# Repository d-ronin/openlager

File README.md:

STM32F4 based logging dongle for **HIGH RATE** logging

This project is inspired by [OpenLog](https://github.com/sparkfun/OpenLog).

*Why do something new?*  To attain higher rates!  The **openlager** hardware can accept data at high rates using slave SPI or fast async serial.  It uses a 4-wide SDIO interface to the card to support higher peak logging rates.  And the reasonable amount of memory buffer on the STM32F411 lets us ride out times when the SD card is busy erasing or doing other housekeeping without losing data.

The **openlager** hardware design and firmware are produced by the [dRonin](http://dronin.org) project, which produces high-quality flight controller software for drone racing and autonomous flight.  To log everything that's happening in a lossless fashion, high rate logs are required.  But we anticipate it being useful for a wide variety of applications.

# Licenses

The **openlager** hardware in `hardware/` is licensed under a Creative Commons Attribution 4.0 International License (CC BY 4.0), as contained in `hardware/LICENSE.txt`

The **openlager** firmware (and bootloader) in `src/`, `loader/`, and `shared/` is licensed under a simplified BSD license as found in `src/LICENSE.txt`

The openlager **logo** may only be used with permission from the dRonin project.

The **fatfs** library in `libs/fatfs` is licensed under the one-clause BSD license as found in the source files in that directory.

The **STM32F4xx_StdPeriph_Driver** library in `libs/STM32F4xx_StdPeriph_Driver` is largely licensed under a restrictive license that limits its usage to ST family processors.  To use this software on non-ST parts, the dependency on this library code must be removed.  Portions of this code (the `core_cm*` include headers) are licensed under a permissive 3 clause BSD license from ARM, as noted in the individual files.

The **mmcreg.h** file from FreeBSD in `libs/inc` is licensed under a simplified BSD license.

The **jsmn** library in `libs` is licensed under the MIT license.

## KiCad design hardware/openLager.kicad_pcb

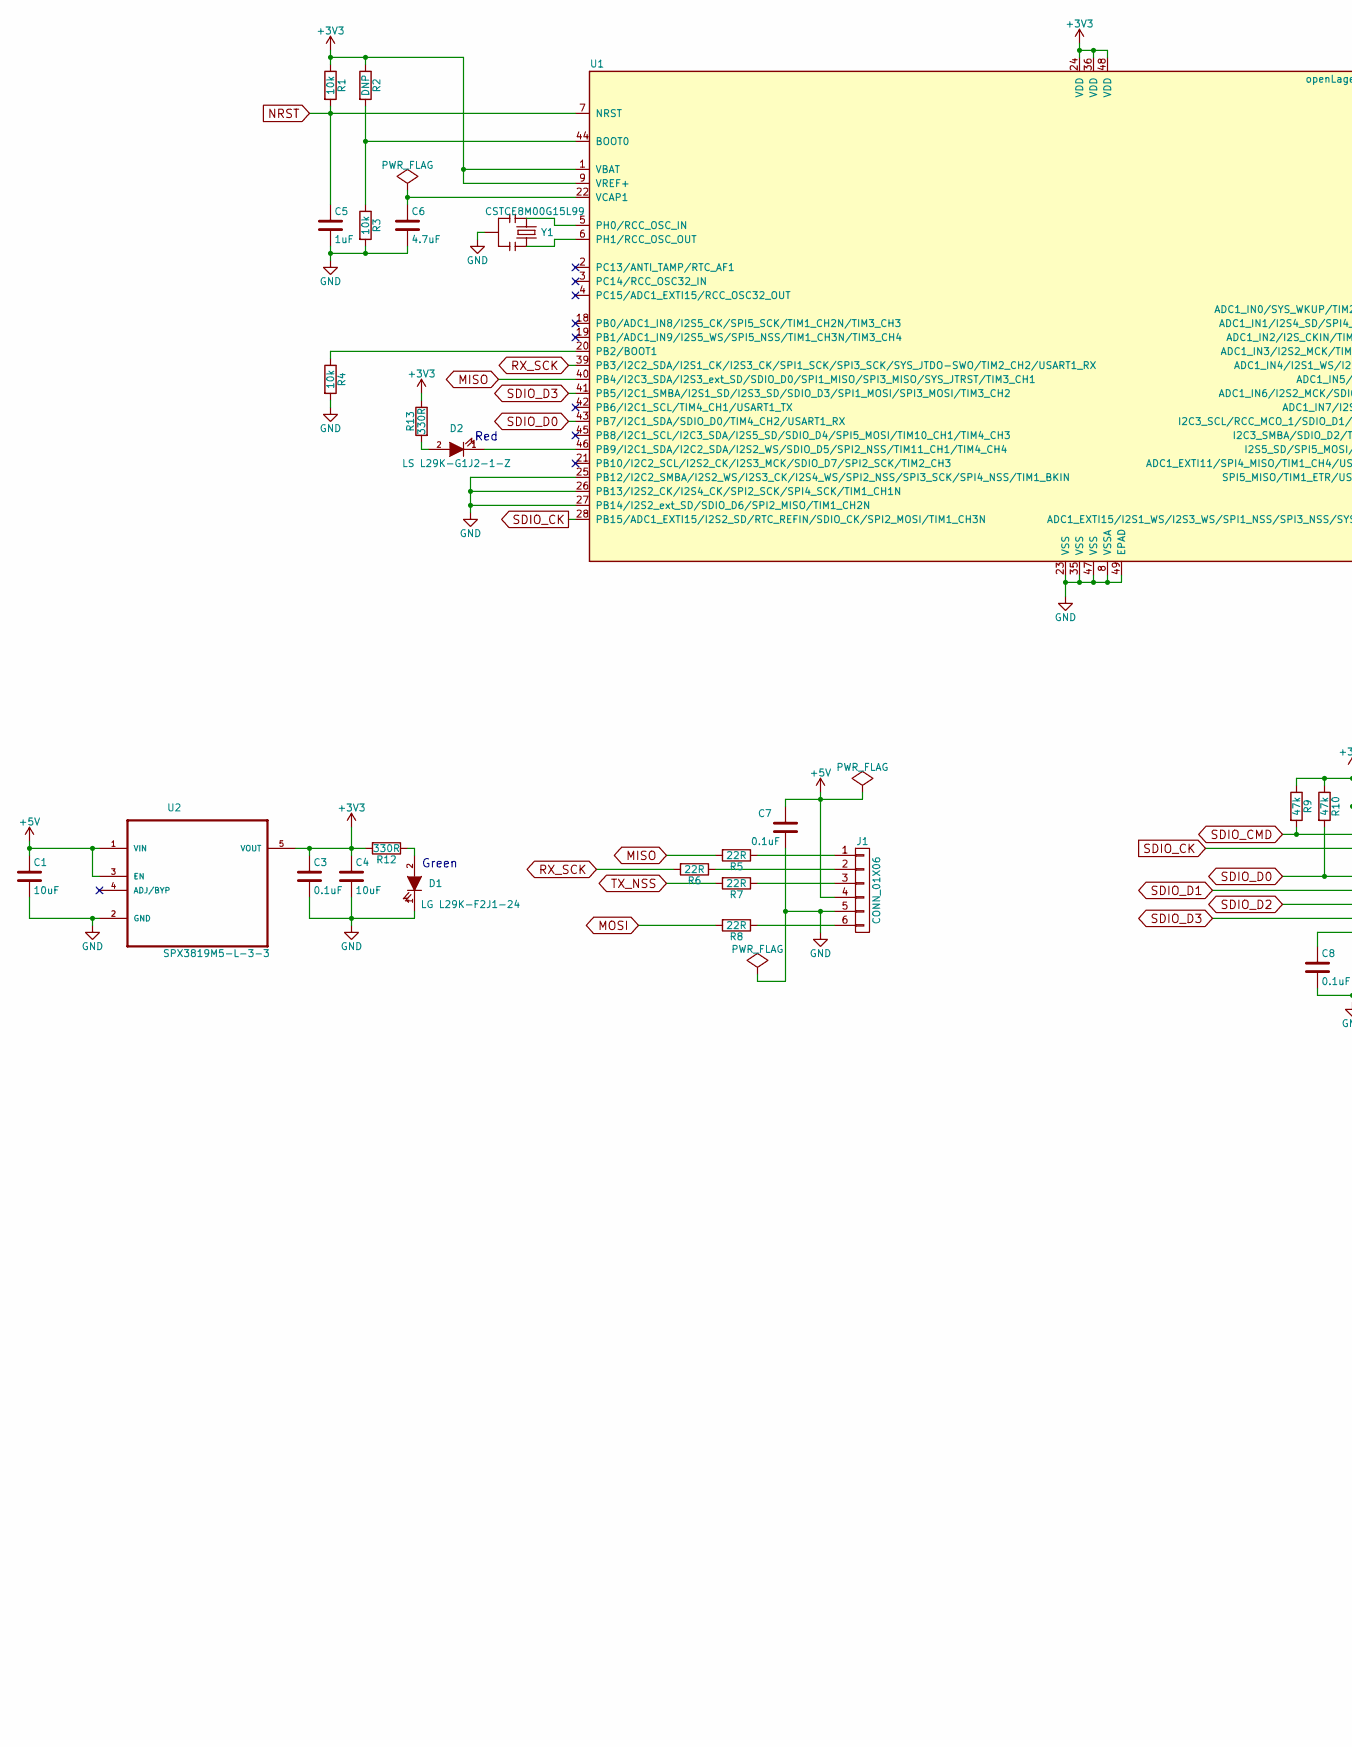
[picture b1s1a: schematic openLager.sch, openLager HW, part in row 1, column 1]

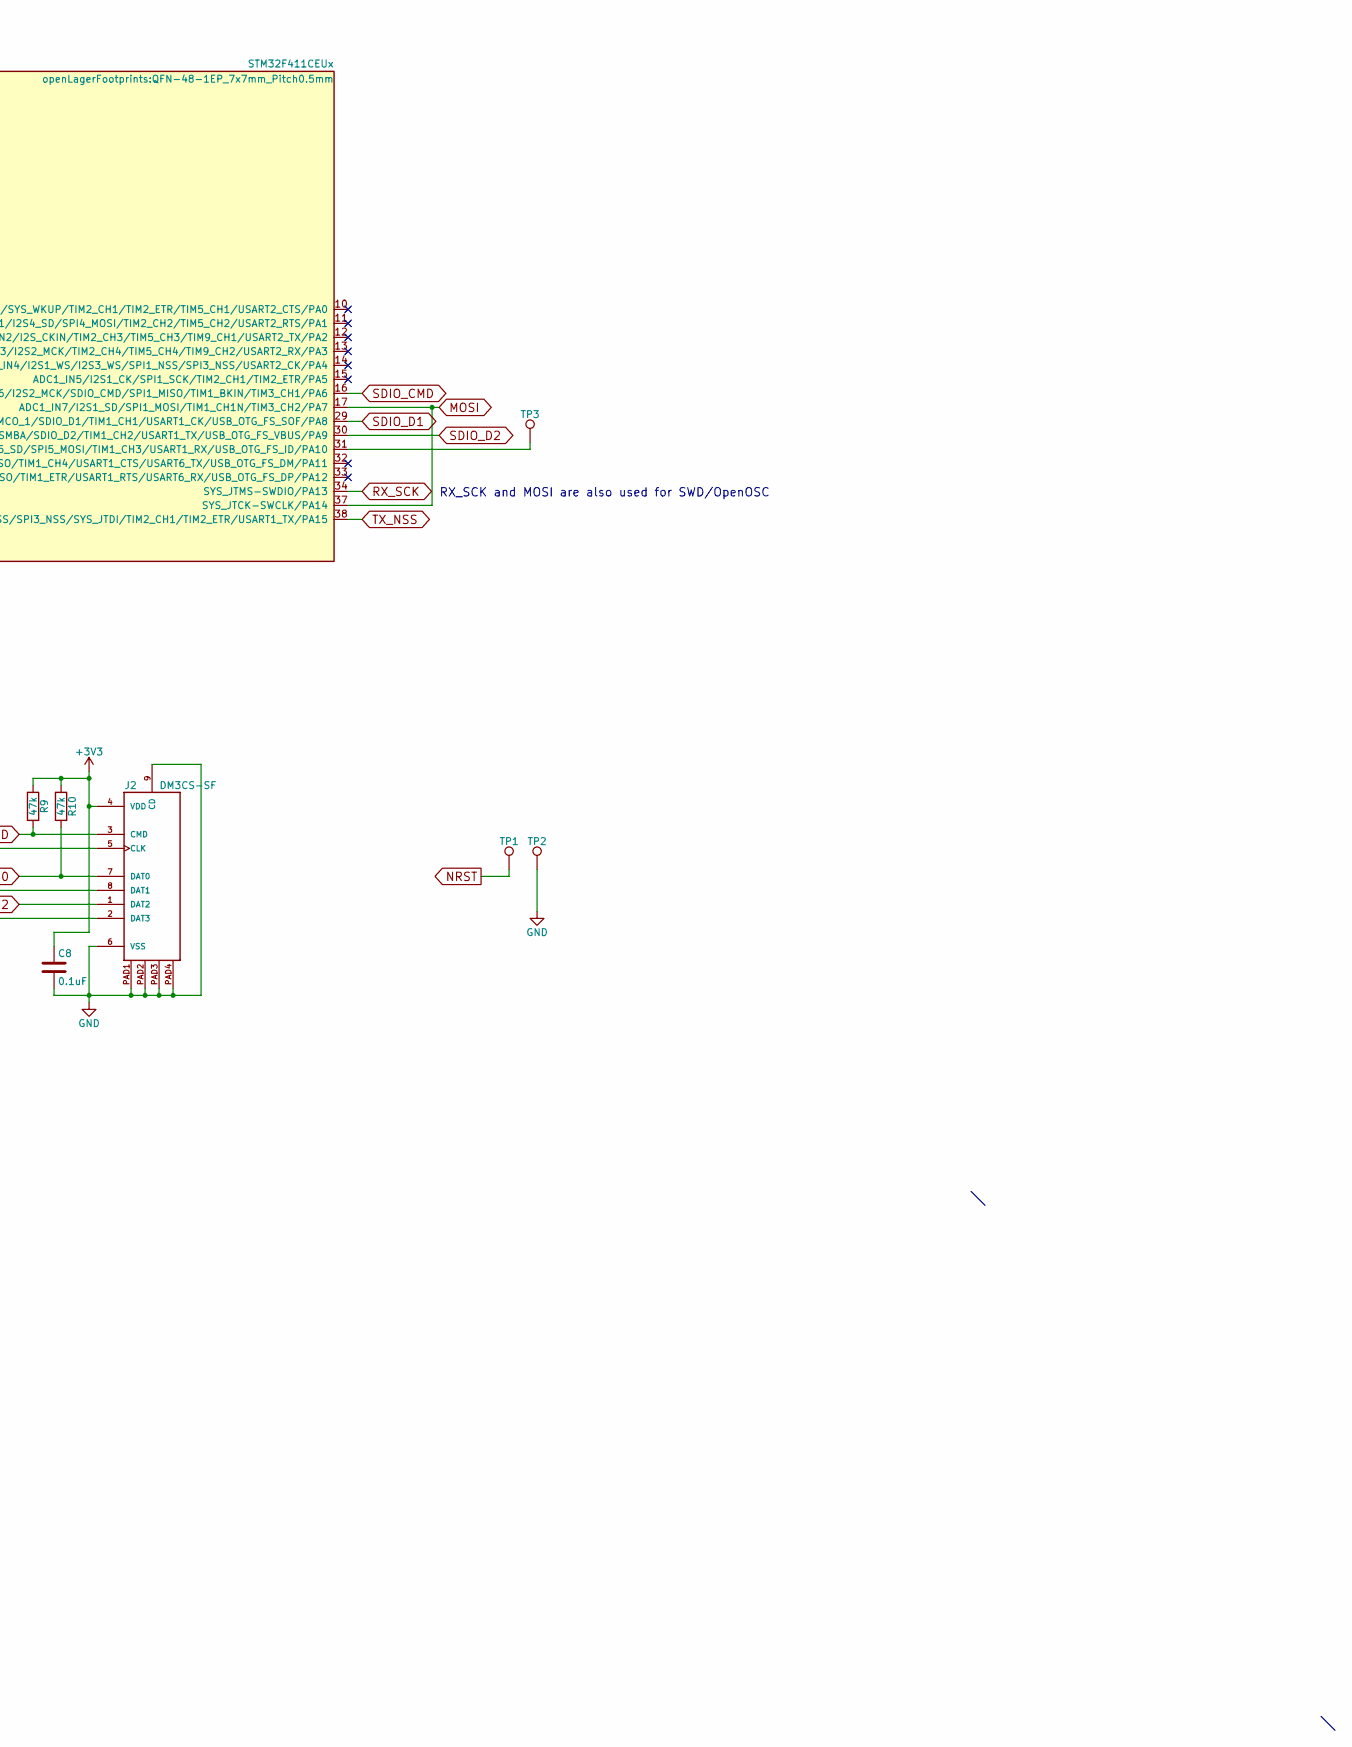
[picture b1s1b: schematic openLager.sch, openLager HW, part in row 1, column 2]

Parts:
C1, C4: 10uF; C_0402; Mfg PN CL05A106MP5NUNC
C3, C7, C8: 0.1uF; C_0402; Mfg PN GRM155R70J104KA01D
C5: 1uF; C_0402; Mfg PN GRM155R70J105MA12D
C6: 4.7uF; C_0402; Mfg PN CL05A475MQ5NQNC
D1: LG L29K-F2J1-24; LED_0603; Mfg PN LG L29K-F2J1-24
D2: LS L29K-G1J2-1-Z; LED_0603; Mfg PN LS L29K-G1J2-1-Z
J1: CONN_01X06; Socket_Strip_Straight_1x06; Mfg PN DNP
J2: DM3CS-SF; HRS_DM3CS-SF; Mfg PN DM3CS-SF
R1, R3, R4: 10k; R_0402; Mfg PN RC0402JR-0710KL
R2: DNP; R_0402; Mfg PN DNP
R5, R6, R7, R8: 22R; R_0402; Mfg PN RC0402JR-0722RL
R9, R10: 47k; R_0402; Mfg PN RC0402JR-0747KL
R12, R13: 330R; R_0402; Mfg PN RC0402JR-07330RL
TP1, TP2, TP3: TEST_1P; TP; Mfg PN DNP
U1: STM32F411CEUx; QFN-48-1EP_7x7mm_Pitch0.5mm; Mfg PN STM32F411CEU6
U2: SPX3819M5-L-3-3; SOT95P280X145-5N; Mfg PN SPX3819M5-L-3-3/TR
Y1: CSTCE8M00G15L99; X3-SMD-3.6X1.3X0.8MM; Mfg PN CSTCE8M00G15L99-R0

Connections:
+3V3: C3.1, C4.1, C8.1, J2.4 (VDD), R1.1, R2.1, R9.1, R10.1, R12.2, R13.1, U1.1 (VBAT), U1.9 (VREF+), U1.24 (VDD), U1.36 (VDD), U1.48 (VDD), U2.5 (VOUT)
+5V: C1.1, C7.1, J1.4, U2.1 (VIN), U2.3 (EN)
GND: C1.2, C3.2, C4.2, C5.2, C6.2, C7.2, C8.2, D1.1 (K), J1.5, J2.6 (VSS), J2.9 (CD), J2.PAD1, J2.PAD2, J2.PAD3, J2.PAD4, R3.2, R4.2, TP2.1, U1.8 (VSSA), U1.23 (VSS), U1.25 (PB12/I2C2_SMBA/I2S2_WS/I2S3_CK/I2S4_WS/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), U1.26 (PB13/I2S2_CK/I2S4_CK/SPI2_SCK/SPI4_SCK/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), U1.27 (PB14/I2S2_ext_SD/SDIO_D6/SPI2_MISO/TIM1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), U1.35 (VSS), U1.47 (VSS), U1.49 (EPAD), U2.2 (GND), Y1.2
MISO: R5.2, U1.40 (PB4/I2C3_SDA/I2S3_ext_SD/SDIO_D0/SPI1_M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)
MOSI: R8.2, U1.17 (ADC1_IN7/I2S1_SD/SPI1_MOSI/TIM1_CH1N/TI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), U1.37 (SYS_JTCK-SWCLK/PA14)
NRST: C5.1, R1.2, TP1.1, U1.7 (NRST)
unnamed: C6.1, U1.22 (VCAP1)
unnamed: D1.2 (A), R12.1
unnamed: D2.1 (K), U1.46 (PB9/I2C1_SDA/I2C2_SDA/I2S2_WS/SDIO_D5/S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)
unnamed: D2.2 (A), R13.2
unnamed: J1.1, R5.1
unnamed: J1.2, R6.1
unnamed: J1.3, R7.1
unnamed: J1.6, R8.1
unnamed: R2.2, R3.1, U1.44 (BOOT0)
unnamed: R4.1, U1.20 (PB2/BOOT1)
unnamed: TP3.1, U1.31 (I2S5_SD/SPI5_MOSI/TIM1_CH3/USART1_RX/US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)
unnamed: U1.5 (PH0/RCC_OSC_IN), Y1.1
unnamed: U1.6 (PH1/RCC_OSC_OUT), Y1.3
RX_SCK: R6.2, U1.34 (SYS_JTMS-SWDIO/PA13), U1.39 (PB3/I2C2_SDA/I2S1_CK/I2S3_CK/SPI1_SCK/S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)
SDIO_CK: J2.5 (CLK), U1.28 (PB15/ADC1_EXTI15/I2S2_SD/RTC_REFIN/SDIO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)
SDIO_CMD: J2.3 (CMD), R9.2, U1.16 (ADC1_IN6/I2S2_MCK/SDIO_CMD/SPI1_MISO/TI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)
SDIO_D0: J2.7 (DAT0), R10.2, U1.43 (PB7/I2C1_SDA/SDIO_D0/TIM4_CH2/USART1_RX)
SDIO_D1: J2.8 (DAT1), U1.29 (I2C3_SCL/RCC_MCO_1/SDIO_D1/TIM1_CH1/USA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)
SDIO_D2: J2.1 (DAT2), U1.30 (I2C3_SMBA/SDIO_D2/TIM1_CH2/USART1_TX/US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)
SDIO_D3: J2.2 (DAT3), U1.41 (PB5/I2C1_SMBA/I2S1_SD/I2S3_SD/SDIO_D3/S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)
TX_NSS: R7.2, U1.38 (ADC1_EXTI15/I2S1_WS/I2S3_WS/SPI1_NSS/SP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)

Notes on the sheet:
Green
Red
RX_SCK and MOSI are also used for SWD/OpenOSC

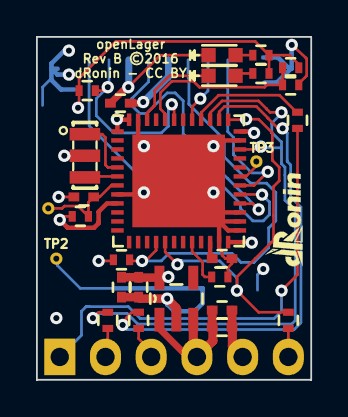
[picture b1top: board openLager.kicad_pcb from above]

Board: 4 copper layers, 15.2 x 19.0 mm, 29 parts (1 on the bottom side), 27 nets.

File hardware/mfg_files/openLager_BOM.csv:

Reference, Quantity, Value, Footprint, Datasheet, Mfg Name, Mfg PN, Link
C1 C4 ,2,10uF,openLagerFootprints:C_0402,http://datasheet.octopart.com/CL05A106MP5NUNC-Samsung-datash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,Samsung,CL05A106MP5NUNC,https://octopart.com/cl05a106mp5nunc-samsung-22457395
C5 ,1,1uF,openLagerFootprints:C_0402,http://datasheet.octopart.com/GRM-Series-Murata-datasheet-fa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,Murata,GRM155R70J105MA12D,https://octopart.com/grm155r70j105ma12d-murata-23261089
C6 ,1,4.7uF,openLagerFootprints:C_0402,http://www.samsungsem.com/kr/support/product-search/mlcc/__i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,Samsung,CL05A475MQ5NQNC,https://octopart.com/cl05a475mq5nqnc-samsung-24957780
C3 C7 C8 ,3,0.1uF,openLagerFootprints:C_0402,http://datasheet.octopart.com/GRM155R70J104KA01D-Murata-data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,Murata,GRM155R70J104KA01D,https://octopart.com/grm155r70j104ka01d-murata-17930200
D1 ,1,LG L29K-F2J1-24,openLagerFootprints:LED_0603,http://datasheet.octopart.com/LG-L29K-F2J1-24-Osram-datashee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,Osram Opto,LG L29K-F2J1-24,https://octopart.com/lg+l29k-f2j1-24-osram+opto-31119809
D2 ,1,LS L29K-G1J2-1-Z,openLagerFootprints:LED_0603,http://datasheet.octopart.com/Q65110A1757-Osram-Opto-datashe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,Osram Opto,LS L29K-G1J2-1-Z,https://octopart.com/ls+l29k-g1j2-1-z-osram+opto-31093939
J1 ,1,CONN_01X06,openLagerFootprints:Socket_Strip_Straight_1x06,DNP,DNP,DNP,DNP
J2 ,1,DM3CS-SF,openLagerFootprints:HRS_DM3CS-SF,http://datasheet.octopart.com/DM3CS-SF-Hirose-datasheet-6229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,Hirose,DM3CS-SF,https://octopart.com/dm3cs-sf-hirose-44525751
R1 R3 R4 ,3,10k,openLagerFootprints:R_0402,http://datasheet.octopart.com/RC0402JR-0710KL-Yageo-datashee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,Yageo,RC0402JR-0710KL,https://octopart.com/rc0402jr-0710kl-yageo-55458470
R12 R13 ,2,330R,openLagerFootprints:R_0402,http://datasheet.octopart.com/RC0402JR-07330RL-Yageo-datashe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,Yageo,RC0402JR-07330RL,https://octopart.com/rc0402jr-07330rl-yageo-40021082
R2 ,1,DNP,openLagerFootprints:R_0402,DNP,DNP,DNP,DNP
R5 R6 R7 R8 ,4,22R,openLagerFootprints:R_0402,http://datasheet.octopart.com/RC0402JR-0722RL-Yageo-datashee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,Yageo,RC0402JR-0722RL,https://octopart.com/rc0402jr-0722rl-yageo-1173206
R10 R9 ,2,47k,openLagerFootprints:R_0402,http://datasheet.octopart.com/RC0402JR-0747KL-Yageo-datashee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,Yageo,RC0402JR-0747KL,https://octopart.com/rc0402jr-0747kl-yageo-39834460
TP1 ,1,TEST_1P,openLagerFootprints:Socket_Strip_Straight_1x01,DNP,DNP,DNP,DNP
TP2 TP3 ,2,TEST_1P,openLagerFootprints:TP,DNP,DNP,DNP,DNP
U1 ,1,STM32F411CEUx,openLagerFootprints:QFN-48-1EP_7x7mm_Pitch0.5mm,http://datasheet.octopart.com/STM32F411CEU6-STMicroelectroni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,ST Microelectronics,STM32F411CEU6,https://octopart.com/stm32f411ceu6-stmicroelectronics-47202664
U2 ,1,SPX3819M5-L-3-3,openLagerFootprints:SOT95P280X145-5N,http://datasheet.octopart.com/SPX3819M5-L-3-3-TR-Exar-datash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,Exar,SPX3819M5-L-3-3/TR,https://octopart.com/spx3819m5-l-3-3%2Ftr-exar-9290124
Y1 ,1,CSTCE8M00G15L99,openLagerFootprints:X3-SMD-3.6X1.3X0.8MM,http://datasheet.octopart.com/CSTCE8M00G15L99-R0-Murata-data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,Murata,CSTCE8M00G15L99-R0,https://octopart.com/cstce8m00g15l99-r0-murata-17751576

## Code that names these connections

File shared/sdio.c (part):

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	// Clocks programmed elsewhere and peripheral/GPIO clock enabled already

	// program GPIO / PinAF
	// SDIO_CK=PB15            SDIO_CMD=PA6
	// SDIO_D0=PB7 SDIO_D1=PA8 SDIO_D2=PA9 SDIO_D3=PB5

	sd_initpin(GPIOA, 6);
	sd_initpin(GPIOA, 8);
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
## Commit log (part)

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2016-04-17 readme: enhance, add logo artwork
2016-04-17 readme: enhance, add logo artwork (#1)
2016-04-17 argh, touch up a dumb typo.
2016-04-17 argh, touch up a dumb typo. (#2)
2016-04-17 introduce fatfs library from upstream R0.12 (#3)
    retrieved from http://elm-chan.org/fsw/ff/00index_e.html
    http://elm-chan.org/fsw/ff/ff12.zip
2016-04-17 Import STM32F4xx_StdPeriph_Driver.
    License was saved from
    http://www.st.com/software_license_agreement_liberty_v2
2016-04-17 Import STM32F4xx_StdPeriph_Driver. (#4)
    License was saved from
    http://www.st.com/software_license_agreement_liberty_v2
2016-04-17 Add license file and license info, reorg tree (#5)
2016-04-18 manually bring in other parts of ST libs
    This stuff was in cmsis_system.
2016-04-18 readme: improve license description
2016-04-18 Add a minimal makefile to compile stuff.
    Does not properly link, linker script, do startup code, etc.
2016-04-18 various work to get some initial files building (#6)
    * manually bring in other parts of ST libs
    This stuff was in cmsis_system.
    * readme: improve license description
    * fatfs: restructure
    Rename the fatfs diskio.c to .example to indicate it's just a stub.
    Make our own copy of this to begin implementing the IO stubs.
2016-04-18 fatfs config: change to a combination that works
    Apparently there are upstream bugs with f_forward.
2016-04-18 Mpl morsels (#7)
    morse library, compilation fixes
2016-04-18 Move license to be consistent with droid's tree
2016-04-18 Get initial startup code and main in
    Produce basic ELF contents, too. Superficially appears correct for this
    trivial case.
2016-04-19 reorganize into separate bootloader and main-program
2016-04-19 reorganize into separate bootloader and main-program (#10)
2016-04-19 various fixes, stub out hardware init
2016-04-19 further work on getting target to start
    * There's a systick handler and provisions for interrupt vectors.
    * The linker script is altered to treat data right.
    * We initialize the PLL and wait for clocks to be operational.
2016-04-19 further work on getting target to start (#12)
    * There's a systick handler and provisions for interrupt vectors.
    * The linker script is altered to treat data right.
    * We initialize the PLL and wait for clocks to be operational.
2016-04-19 Initial draft of HW for review
2016-04-19 Minor tweaks as per @mlyle review
2016-04-19 Initial hw files (#8)
    * Initial draft of HW for review
    * Adding the design and output files
    * Minor tweaks as per @mlyle review
2016-04-19 Makefile now works on Win 10 and gitingore updated
2016-04-19 Teach makefile to make bin files with objcopy
2016-04-19 Disable floating point init for now
    This allows GNU-ARM-Eclipse-QEMU to emulate the board without failing
    out.
    Command line I'm currently using is:
    `/Applications/GNU\ ARM\ Eclipse/QEMU/2.4.50-201510290935-dev/bin/qemu-system-gnuarmeclipse -board NUCLEO-F411RE -image build/openloader.bin`
2016-04-19 Get running in emulator (#14)
    * Teach makefile to make bin files with objcopy
    * Disable floating point init for now
    This allows GNU-ARM-Eclipse-QEMU to emulate the board without failing
    out.
    Command line I'm currently using is:
    `/Applications/GNU\ ARM\ Eclipse/QEMU/2.4.50-201510290935-dev/bin/qemu-system-gnuarmeclipse -board NUCLEO-F411RE -image build/openloader.bin`
2016-04-19 openloader: get to the point where it can blink LED (#15)
2016-04-19 Many changes towards bootloader support
    * Pad firmware images to full size with 0xff
    * Add new ef_lager.bin which is the "entire firmware" like dR.
    * Implement new invoke_next_program in loader which chains to the
    next program
    * Synchronized code between openloader and openlager.
    * Adjust LED blink behavior so I can tell the difference between
2016-04-19 Stub out beginning of SDIO periph support.
2016-04-19 Many changes towards functional bootloader support. (#16)
    * Pad firmware images to full size with 0xff
    * Add new ef_lager.bin which is the "entire firmware" like dR.
    * Implement new invoke_next_program in loader which chains to the
    next program
    * Synchronized code between openloader and openlager.
    * Adjust LED blink behavior so I can tell the difference between
2016-04-20 Bring in mmcreg.h from FreeBSD because it's awesome
2016-04-20 Stub out the beginning of a sd implementation
2016-04-20 readme: mention other places code is stored
2016-04-20 misc work in progress on SDIO (#18)
    * readme: mention other places code is stored
    * work on SDIO towards init and enumeration
2016-04-20 Note using openlager logo requires permission
2016-04-20 sdio: get the code to perhaps be ready to init
2016-04-20 teach loader to send some morse for bringup
2016-04-20 sdio: correct pin af initialization
2016-04-20 adjust to do LED on discovery board
2016-04-20 sdio: completes init sequence successfully
2016-04-20 sdio: completes init sequence successfully (#20)
2016-04-21 sdio/loader: now to the point it can read a file
    It flashes out Alice's Adventures in Wonderland in morse code with
    this current version from the bootloader.
2016-04-21 alter startup code to properly set vector loc
2016-04-21 Make filenames more fun
2016-04-21 The loader is now a complete loader
2016-04-21 make: compile with -Werror, we're clean
2016-04-21 clocking: clock at cpu=96MHz sd=38.4MHz apb1=48MHz
    Still uses the internal oscillator as the PLL source while on
    development hardware.
2016-04-21 Main program (not loader) runs with faster clock (#23)
    * make: compile with -Werror, we're clean
    * clocking: clock at cpu=96MHz sd=38.4MHz apb1=48MHz
    Still uses the internal oscillator as the PLL source while on
    development hardware.
2016-04-21 Build using ccache if possible, to compile fast
2016-04-21 Add jsmn library to source code
2016-04-23 improve shared code structure, adjust namespaces
2016-04-23 Stub out code to disable the SWD pins
2016-04-23 Fixups for USART support
2016-04-23 Blink an error when external osc does not start
2016-04-23 adjust fatfs config for performance
2016-04-23 led: store speed to send morse in led module
2016-04-23 add sd write path
2016-04-23 add config file processing stub
2016-04-23 config: improve the default config write process
2016-04-23 assorted work, getting write path to SD functional (#25)
    * adjust fatfs config for performance
    * led: store speed to send morse in led module
    * add sd write path
    * add config file processing stub
    * correct clock frequency when using ext osc
    * config: improve the default config write process
2016-04-23 sdio: use flow control; prevent overruns/underruns
2016-04-24 Teach makefile to gather stack usage information
    (Triggered by building as `STACK_USAGE=1 make`)
2016-04-24 makefile: teach to gather the data+BSS size
    Now evaluating the total memory usage gets relatively easy.
2016-04-24 stack anal: reorder output, detect interrupt handlers
2016-04-24 stack and memory analysis, plus small additional work towards logging (#26)
    * sdio: use flow control; prevent overruns/underruns
    * Add stack analysis stuff.
    It works! My command lines look like:
    ```
    make clean
    STACK_USAGE=1 make -j4
2016-04-25 Add rudimentary USART RX code.
2016-04-25 Add basic log-file selection logic.
2016-04-25 add minimal logging code
2016-04-25 Minimally implement fatfs diskio "sync"
    Since we don't buffer / cache this doesn't need to do anything.
2016-04-25 sdio: disable hardware flow control, adjust timeouts
2016-04-25 Properly enable USART interrupts
2016-04-25 Fix an off by one error in USART buffer management
2016-04-25 Make it actually work as a logger (#27)
    * Add rudimentary USART RX code.
    * Add basic log-file selection logic.
    * usart: Add RX API call
    * add minimal logging code
    * Minimally implement fatfs diskio "sync"
    Since we don't buffer / cache this doesn't need to do anything.
2016-04-25 Teach to abort transfers and retry on failure
2016-04-25 Add retries to SD layer (#31)
    * Turn off SD morse debugging
    * Teach to abort transfers and retry on failure
2016-04-25 Add ST errata note to sdio.c.
2016-04-25 Clean up Link on J1 and TP*
2016-04-25 Disable SWD once firmware running / out of reset
2016-04-25 Adding BOM and tweaked solder paste layer (#35)
    * Adding BOM and tweaked solder paste layer
    * Clean up Link on J1 and TP*
2016-04-26 add configuration support
2016-04-26 add configuration support (#38)
    Performance was validated at 1,152,000 bps with no drops on a 4 megabyte log. at 1,500,000 bps we still lose some on prototype hardware (1x SDIO) with no DMA enabled and no multiple-block writes.
2016-04-26 uncrustify all the code
    Thankfully this has resulted in minimal change to the code, mostly in
    bracket conventions after function definitions and spaces (instead of
    tabs) for alignment of comments.
2016-04-27 DFM changes and added SS RefDes
2016-04-27 DFM changes and added SS RefDes (#41)
2016-04-28 Put dRonin logo on board
2016-04-28 Put dRonin logo on board (#42)
2016-05-02 Introduce support for DMA on write.
    Fixes #30.
2016-05-02 Introduce support for DMA on write. (#44)
    Fixes #30.
2016-05-02 hw: bom: Adjust format to one-line-per-PN (#43)
    So that multiple refdeses can be on one line. Easier to place from,
    plays nicer with OctoPart.
2016-05-02 sdio: just set blocklen once, when first talking to card
    less turnarounds / round trips are good
2016-05-02 use multiple block write command
2016-05-02 Performance improvements (#45)
    * don't try to write more than 40k in a transaction
    If the buffer is really full, don't try to drain it all at once.
    Because it's important to pick a sane-sized transaction that we can
    complete and free buffer sooner. (Tradeoff throughput vs. time-till-
    some-of-the-buffer-is-freed).
    * sdio: just set blocklen once, when first talking to card
2016-05-03 add preallocation infrastructure
    can either update file / claim space immediately to lower write
    amplification, or can just find a contiguous section of desired size.
2016-05-03 Write slightly longer chunks at a time.
2016-05-03 increase buffer size by 25%
    Huzzah having stack analysis and no RTOS for this simple stuff, because
    it lets us squeeze every bit out of the hardware.
    Analysis says:
    Memory used by data+BSS: 644
    Peak execution estimate (main + worst-case IV):
    main = 128992, worst IV = 24, total = 129016
2016-05-07 move LED and LED sense to non-eval hardware config
2016-05-10 loader: also move to production hw config
2016-05-10 move LED and LED sense to non-eval hardware config (#47)
    * move LED and LED sense to non-eval hardware config
    * loader: also move to production hw config
2016-05-10 loader: woops: fix it so LED actually works (#49)
2016-05-15 Updated to RevB, changed LED and SS
2016-05-15 Adding new BOM
2016-05-17 Change /NRST from pin to TP
2016-05-19 Hardware rev b (#50)
    * Updated to RevB, changed LED and SS
    * Adding new BOM
    * Changing SCH rev
    * Change /NRST from pin to TP
2016-06-16 Add (very simple) fab drawing to openlager.
2016-06-22 Add built-in self test mode to openlager.
    To be used in manufacturing/fulfillment. It's really simple right now:
    write 6 megabytes of data to a filesystem, read it back, blink LEDs.
2016-06-29 Add built-in self test mode to openlager. (#52)
    To be used in manufacturing/fulfillment. It's really simple right now:
    write 6 megabytes of data to a filesystem, read it back, blink LEDs.

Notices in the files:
shared/sdio.c:
Copyright (c) 2016, dRonin
All rights reserved.
hardware/openLager.kicad_pcb:
Rev B ©2016
dRonin - CC BY
hardware/openLager.sch:
work. If not, see http://creativecommons.org/licenses/by/4.0
openLager HW is licensed under a Creative Commons Attribution 4.0 International License
